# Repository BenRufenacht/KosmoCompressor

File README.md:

# KosmoCompressor
 Kosmo Version of the Moritz Klein Compressor

[Build Docs from Moritz Klein (Erika Synths)](https://www.ericasynths.lv/media/COMPRESSOR_MANUAL.pdf)

Status:   
January 2024 - First run of manufacturing found some minor mistakes that were fixed, but the updates to the pcbs have not been tested.

License:  
[CC-BY-SA](https://creativecommons.org/licenses/by-sa/3.0/)

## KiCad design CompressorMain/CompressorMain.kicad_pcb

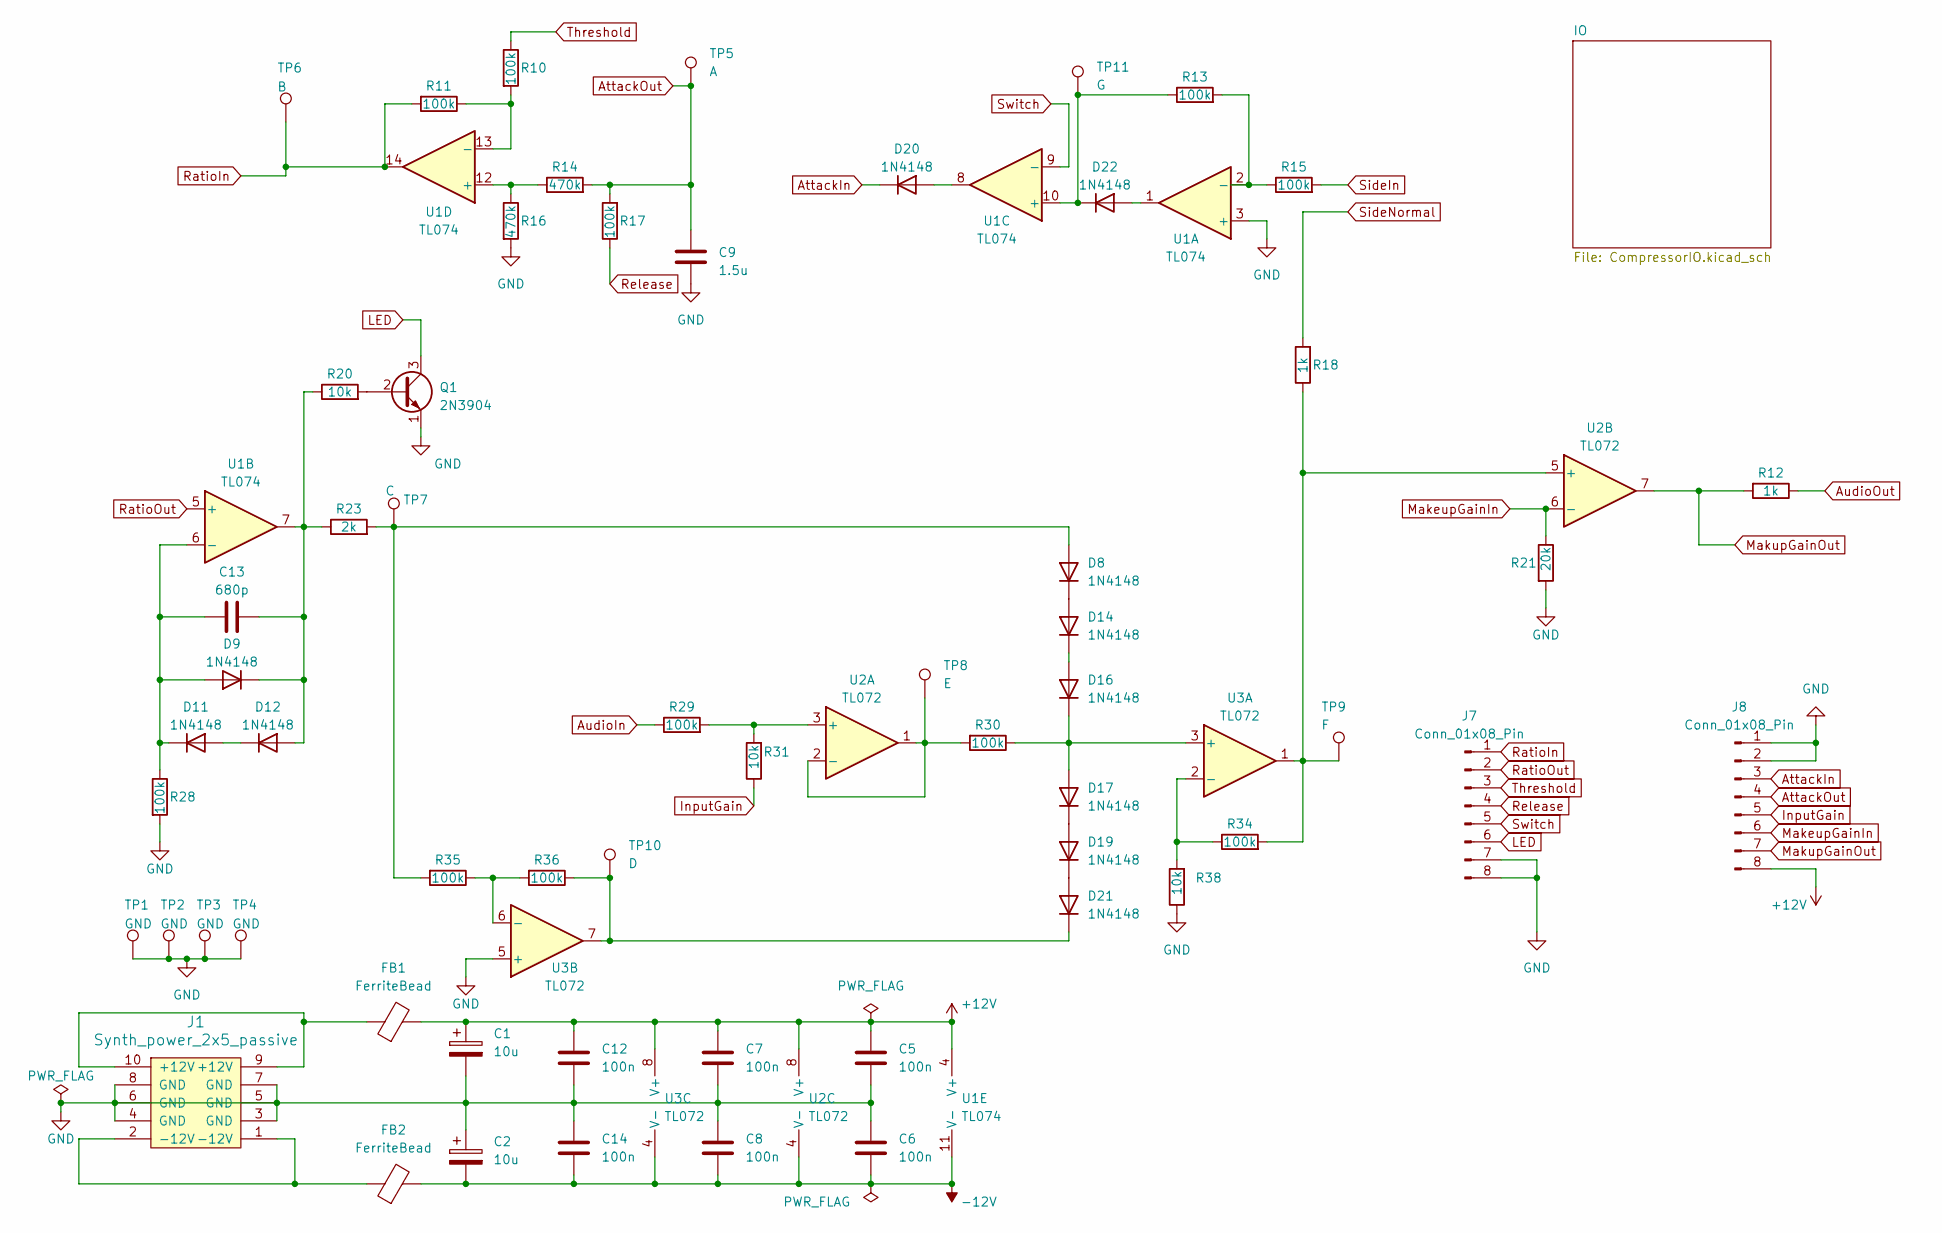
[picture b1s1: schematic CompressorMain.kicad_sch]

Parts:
C1, C2: 10u; CP_Radial_D6.3mm_P2.50mm
C5, C6, C7, C8, C12, C14: 100n; C_Disc_D3.0mm_W1.6mm_P2.50mm
C9: 1.5u; C_Rect_L7.2mm_W4.5mm_P5.00mm_FKS2_FKP2_MKS2_MKP2
C13: 680p; C_Disc_D3.0mm_W1.6mm_P2.50mm
D8, D9, D11, D12, D14, D16, D17, D19, D20, D21, D22: 1N4148; D_DO-35_SOD27_P7.62mm_Horizontal
FB1, FB2: FerriteBead; FB_Axial_L5.0mm_D3.6mm_P10.00mm
J1: Synth_power_2x5_passive; Power_Header
J7, J8: Conn_01x08_Pin; PinSocket_1x08_P2.54mm_Vertical
Q1: 2N3904; TO-92_Inline_Wide
R10, R11, R13, R15, R17, R28, R29, R30, R34, R35, R36: 100k; R_Axial_DIN0207_L6.3mm_D2.5mm_P10.16mm_Horizontal
R12, R18: 1k; R_Axial_DIN0207_L6.3mm_D2.5mm_P10.16mm_Horizontal
R14, R16: 470k; R_Axial_DIN0207_L6.3mm_D2.5mm_P10.16mm_Horizontal
R20, R31, R38: 10k; R_Axial_DIN0207_L6.3mm_D2.5mm_P10.16mm_Horizontal
R21: 20k; R_Axial_DIN0207_L6.3mm_D2.5mm_P10.16mm_Horizontal
R23: 2k; R_Axial_DIN0207_L6.3mm_D2.5mm_P10.16mm_Horizontal
TP1, TP2, TP3, TP4: GND; TestPoint_THTPad_D1.5mm_Drill0.7mm
TP5: A; TestPoint_THTPad_D1.5mm_Drill0.7mm
TP6: B; TestPoint_THTPad_D1.5mm_Drill0.7mm
TP7: C; TestPoint_THTPad_D1.5mm_Drill0.7mm
TP8: E; TestPoint_THTPad_D1.5mm_Drill0.7mm
TP9: F; TestPoint_THTPad_D1.5mm_Drill0.7mm
TP10: D; TestPoint_THTPad_D1.5mm_Drill0.7mm
TP11: G; TestPoint_THTPad_D1.5mm_Drill0.7mm
U1: TL074; DIP-14_W7.62mm_Socket_LongPads
U2, U3: TL072; DIP-8_W7.62mm_Socket_LongPads

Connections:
+12V: C1.1, C5.1, C7.1, C12.1, FB1.2, J8.8, U1.4 (V+), U2.8 (V+), U3.8 (V+)
-12V: C2.2, C6.2, C8.2, C14.2, FB2.2, U1.11 (V-), U2.4 (V-), U3.4 (V-)
AttackIn: D20.1 (K), J8.3
AttackOut: C9.1, J8.4, R14.2, R17.2, TP5.1
AudioIn: R29.1; also elsewhere on the board
AudioOut: R12.1; also elsewhere on the board
GND: C1.2, C2.1, C5.2, C6.1, C7.2, C8.1, C9.2, C12.2, C14.1, J1.3 (GND), J1.4 (GND), J1.5 (GND), J1.6 (GND), J1.7 (GND), J1.8 (GND), J7.7, J7.8, J8.1, J8.2, Q1.1 (E), R16.2, R21.2, R28.2, R38.1, TP1.1, TP2.1, TP3.1, TP4.1, U1.3 (+), U3.5 (+); also elsewhere on the board
InputGain: J8.5, R31.1
LED: J7.6, Q1.3 (C)
MakeupGainIn: J8.6, R21.1, U2.6 (-)
MakupGainOut: J8.7, R12.2, U2.7
unnamed: D8.2 (A), R23.2, R35.2, TP7.1
unnamed: D11.2 (A), D12.1 (K)
unnamed: C13.1, D9.2 (A), D11.1 (K), R28.1, U1.6 (-)
unnamed: C13.2, D9.1 (K), D12.2 (A), R20.1, R23.1, U1.7
unnamed: D8.1 (K), D14.2 (A)
unnamed: D14.1 (K), D16.2 (A)
unnamed: D16.1 (K), D17.2 (A), R30.1, U3.3 (+)
unnamed: D17.1 (K), D19.2 (A)
unnamed: D19.1 (K), D21.2 (A)
unnamed: D20.2 (A), U1.8
unnamed: D21.1 (K), R36.1, TP10.1, U3.7
unnamed: D22.2 (A), U1.1
unnamed: D22.1 (K), R13.1, TP11.1, U1.10 (+)
unnamed: FB1.1, J1.9 (+12V), J1.10 (+12V)
unnamed: FB2.1, J1.1 (-12V), J1.2 (-12V)
unnamed: Q1.2 (B), R20.2
unnamed: R13.2, R15.1, U1.2 (-)
unnamed: R14.1, R16.1, U1.12 (+)
unnamed: R10.2, R11.1, U1.13 (-)
unnamed: R29.2, R31.2, U2.3 (+)
unnamed: R30.2, TP8.1, U2.1, U2.2 (-)
unnamed: R18.1, R34.2, TP9.1, U2.5 (+), U3.1
unnamed: R34.1, R38.2, U3.2 (-)
unnamed: R35.1, R36.2, U3.6 (-)
RatioIn: J7.1, R11.2, TP6.1, U1.14
RatioOut: J7.2, U1.5 (+)
Release: J7.4, R17.1
SideIn: R15.2; also elsewhere on the board
SideNormal: R18.2; also elsewhere on the board
Switch: J7.5, U1.9 (-)
Threshold: J7.3, R10.1

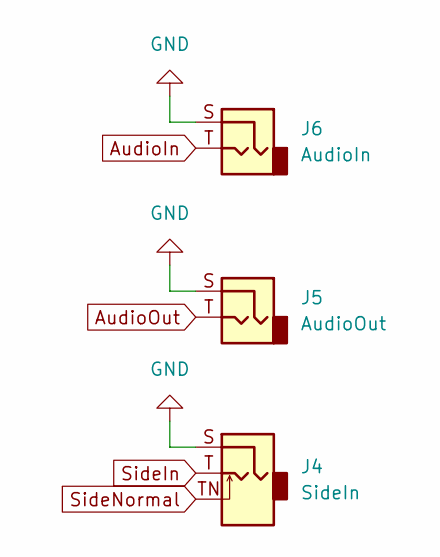
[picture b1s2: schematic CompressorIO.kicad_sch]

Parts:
J4: SideIn; Jack_6.35mm_PJ_629HAN_slots
J5: AudioOut; Jack_6.35mm_PJ_629HAN_slots
J6: AudioIn; Jack_6.35mm_PJ_629HAN_slots

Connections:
AudioIn: J6.T; also elsewhere on the board
AudioOut: J5.T; also elsewhere on the board
GND: J4.S, J5.S, J6.S; also elsewhere on the board
SideIn: J4.T; also elsewhere on the board
SideNormal: J4.TN; also elsewhere on the board

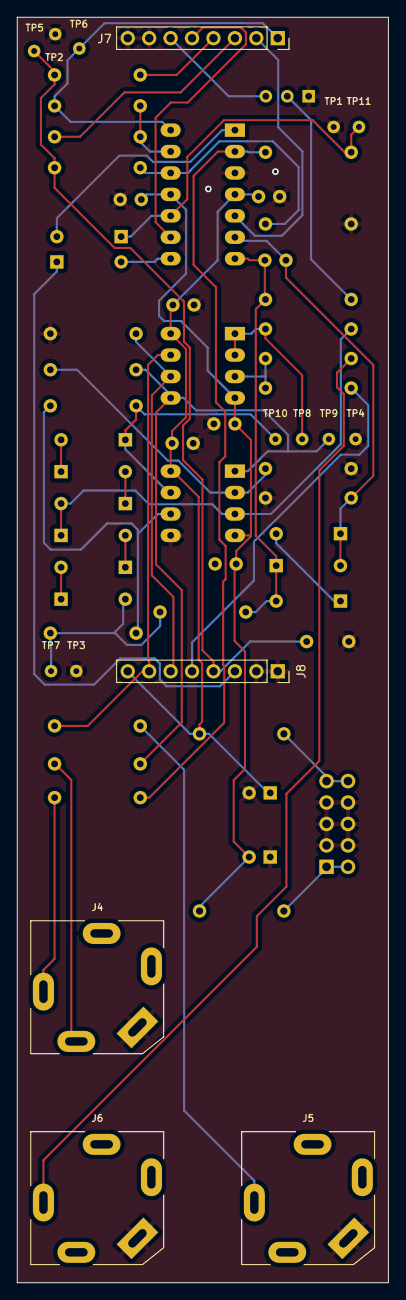
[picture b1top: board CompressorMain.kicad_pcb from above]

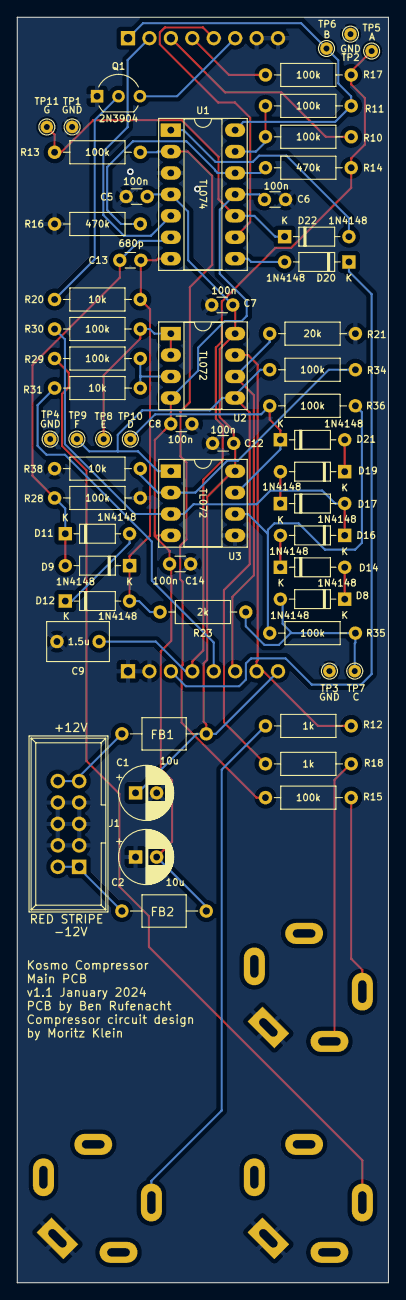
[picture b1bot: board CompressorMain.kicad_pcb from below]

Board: 2 copper layers, 44.0 x 150.0 mm, 64 parts (59 on the bottom side), 42 nets.

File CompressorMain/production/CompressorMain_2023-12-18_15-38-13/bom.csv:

Designator,Footprint,Quantity,Value,LCSC Part #
"C1, C2",CP_Radial_D6.3mm_P2.50mm,2,10u,
"C12, C14, C5, C6, C7, C8",C_Disc_D3.0mm_W1.6mm_P2.50mm,6,100n,
C13,C_Disc_D3.0mm_W1.6mm_P2.50mm,1,680p,
C9,C_Rect_L7.2mm_W2.5mm_P5.00mm_FKS2_FKP2_MKS2_MKP2,1,1.5u,
"D11, D12, D14, D16, D17, D19, D20, D21, D22, D8, D9",D_DO-35_SOD27_P7.62mm_Horizontal,11,1N4148,
"FB1, FB2",FB_Axial_L5.0mm_D3.6mm_P10.00mm,2,FerriteBead,
J1,Power_Header,1,Synth_power_2x5_passive,
J4,Jack_6.35mm_PJ_629HAN_slots,1,SideIn,
J5,Jack_6.35mm_PJ_629HAN_slots,1,AudioOut,
J6,Jack_6.35mm_PJ_629HAN_slots,1,AudioIn,
"J7, J8",PinSocket_1x08_P2.54mm_Vertical,2,Conn_01x08_Pin,
Q1,TO-92_Inline_Wide,1,2N3904,
"R10, R11, R13, R15, R17, R28, R29, R30, R34, R35, R36",R_Axial_DIN0207_L6.3mm_D2.5mm_P10.16mm_Horizontal,11,100k,
"R12, R18",R_Axial_DIN0207_L6.3mm_D2.5mm_P10.16mm_Horizontal,2,1k,
"R14, R16",R_Axial_DIN0207_L6.3mm_D2.5mm_P10.16mm_Horizontal,2,470k,
"R20, R31, R38",R_Axial_DIN0207_L6.3mm_D2.5mm_P10.16mm_Horizontal,3,10k,
R21,R_Axial_DIN0207_L6.3mm_D2.5mm_P10.16mm_Horizontal,1,20k,
R23,R_Axial_DIN0207_L6.3mm_D2.5mm_P10.16mm_Horizontal,1,2k,
U1,DIP-14_W7.62mm_Socket_LongPads,1,TL074,
"U2, U3",DIP-8_W7.62mm_Socket_LongPads,2,TL072,

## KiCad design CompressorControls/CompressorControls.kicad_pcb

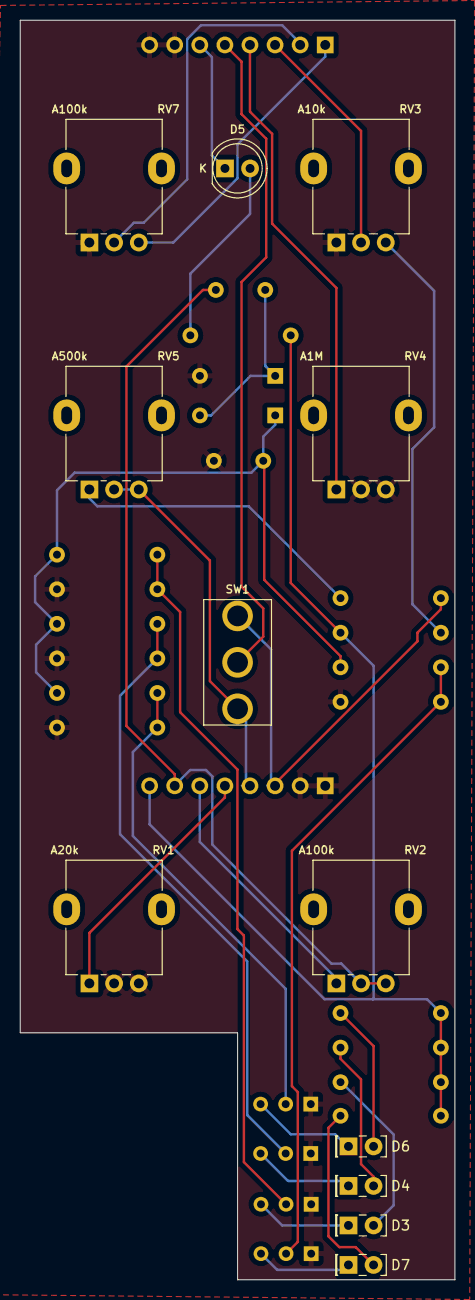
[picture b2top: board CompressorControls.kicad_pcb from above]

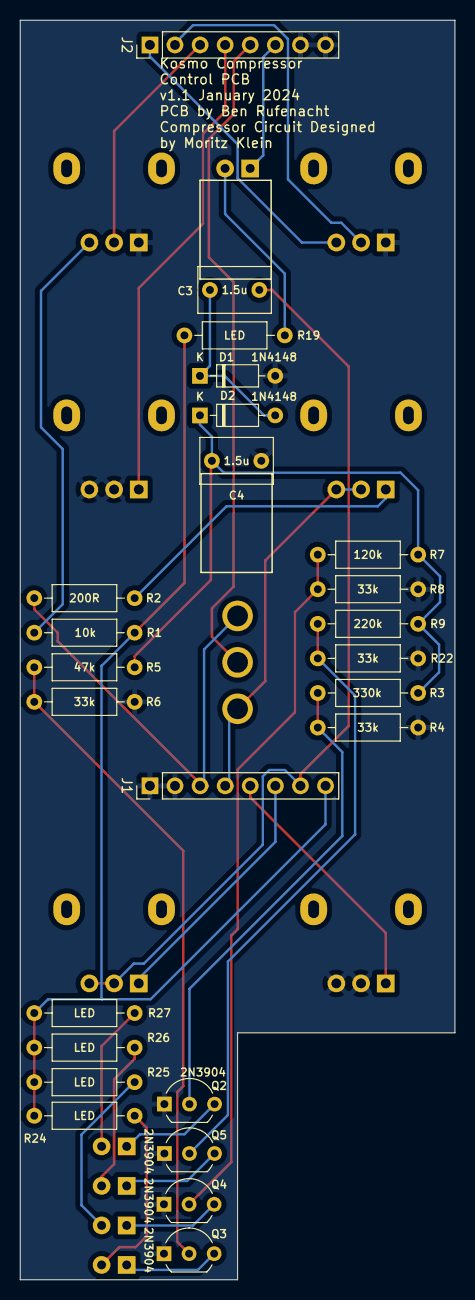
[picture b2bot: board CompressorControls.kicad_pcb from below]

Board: 2 copper layers, 44.0 x 127.5 mm, 37 parts (25 on the bottom side), 30 nets.

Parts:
C3, C4: 1.5u; C_Rect_L7.2mm_W4.5mm_P5.00mm_FKS2_FKP2_MKS2_MKP2
D1, D2: 1N4148; D_DO-35_SOD27_P7.62mm_Horizontal
D3, D7: LED_green; LED_Rectangular_W5.0mm_H2.0mm
D4, D6: LED; LED_Rectangular_W5.0mm_H2.0mm
D5: LED_green; LED_D5.0mm
J1, J2: Conn_01x08_Pin; PinHeader_1x08_P2.54mm_Vertical
Q2, Q3, Q4, Q5: 2N3904; TO-92_Inline_Wide
R1: 10k; R_Axial_DIN0207_L6.3mm_D2.5mm_P10.16mm_Horizontal
R2: 200R; R_Axial_DIN0207_L6.3mm_D2.5mm_P10.16mm_Horizontal
R3: 330k; R_Axial_DIN0207_L6.3mm_D2.5mm_P10.16mm_Horizontal
R4, R6, R8, R22: 33k; R_Axial_DIN0207_L6.3mm_D2.5mm_P10.16mm_Horizontal
R5: 47k; R_Axial_DIN0207_L6.3mm_D2.5mm_P10.16mm_Horizontal
R7: 120k; R_Axial_DIN0207_L6.3mm_D2.5mm_P10.16mm_Horizontal
R9: 220k; R_Axial_DIN0207_L6.3mm_D2.5mm_P10.16mm_Horizontal
R19, R24, R25, R26, R27: LED; R_Axial_DIN0207_L6.3mm_D2.5mm_P10.16mm_Horizontal
RV1: A20k; Potentiometer_Alpha_RD901F-40-00D_Single_Vertical_centered
RV2, RV7: A100k; Potentiometer_Alpha_RD901F-40-00D_Single_Vertical_centered
RV3: A10k; Potentiometer_Alpha_RD901F-40-00D_Single_Vertical_centered
RV4: A1M; Potentiometer_Alpha_RD901F-40-00D_Single_Vertical_centered
RV5: A500k; Potentiometer_Alpha_RD901F-40-00D_Single_Vertical_centered
SW1: SW_SPDT; SPDT-toggle-switch-1M-series

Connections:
+12V: J1.8, R1.1, R19.1, R24.1, R25.1, R26.1, R27.1
AttackIn: J1.3, R2.2, SW1.3 (C)
AttackOut: J1.4, RV5.2, RV5.3, SW1.1 (A)
GND: C4.1, D1.2 (A), J1.1, J1.2, J2.7, J2.8, Q2.1 (E), Q3.1 (E), Q4.1 (E), Q5.1 (E), R4.2, R6.2, R8.2, R22.2, RV1.2, RV1.3, RV3.1, RV4.2, RV4.3, RV7.1
InputGain: J1.5, RV1.1
LED: D5.1 (K), J2.6
MakeupGainIn: J1.6, RV2.1
MakupGainOut: C3.1, J1.7, RV2.2, RV2.3
unnamed: C3.2, D1.1 (K), D2.2 (A)
unnamed: C4.2, D2.1 (K), R3.2, R5.2, R7.2, R9.2
unnamed: D3.2 (A), R25.2
unnamed: D3.1 (K), Q4.3 (C)
unnamed: D4.2 (A), R26.2
unnamed: D4.1 (K), Q5.3 (C)
unnamed: D5.2 (A), R19.2
unnamed: D6.2 (A), R27.2
unnamed: D6.1 (K), Q2.3 (C)
unnamed: D7.2 (A), R24.2
unnamed: D7.1 (K), Q3.3 (C)
unnamed: Q2.2 (B), R3.1, R4.1
unnamed: Q3.2 (B), R5.1, R6.1
unnamed: Q4.2 (B), R7.1, R8.1
unnamed: Q5.2 (B), R9.1, R22.1
unnamed: R1.2, RV3.3
unnamed: R2.1, RV5.1
RatioIn: J2.1, RV7.3
RatioOut: J2.2, RV7.2
Release: J2.4, RV4.1
Switch: J2.5, SW1.2 (B)
Threshold: J2.3, RV3.2

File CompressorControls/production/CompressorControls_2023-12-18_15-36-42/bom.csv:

Designator,Footprint,Quantity,Value,LCSC Part #
"C3, C4",C_Rect_L7.2mm_W2.5mm_P5.00mm_FKS2_FKP2_MKS2_MKP2,2,1.5u,
"D1, D2",D_DO-35_SOD27_P7.62mm_Horizontal,2,1N4148,
"D3, D7",LED_Rectangular_W5.0mm_H2.0mm,2,LED_green,
"D4, D6",LED_Rectangular_W5.0mm_H2.0mm,2,LED,
D5,LED_D5.0mm,1,LED_green,
"J1, J2",PinHeader_1x08_P2.54mm_Vertical,2,Conn_01x08_Pin,
"Q2, Q3, Q4, Q5",TO-92_Inline_Wide,4,2N3904,
R1,R_Axial_DIN0207_L6.3mm_D2.5mm_P10.16mm_Horizontal,1,10k,
"R19, R24, R25, R26, R27",R_Axial_DIN0207_L6.3mm_D2.5mm_P10.16mm_Horizontal,5,LED,
R2,R_Axial_DIN0207_L6.3mm_D2.5mm_P10.16mm_Horizontal,1,200R,
"R22, R4, R6, R8",R_Axial_DIN0207_L6.3mm_D2.5mm_P10.16mm_Horizontal,4,33k,
R3,R_Axial_DIN0207_L6.3mm_D2.5mm_P10.16mm_Horizontal,1,330k,
R5,R_Axial_DIN0207_L6.3mm_D2.5mm_P10.16mm_Horizontal,1,47k,
R7,R_Axial_DIN0207_L6.3mm_D2.5mm_P10.16mm_Horizontal,1,120k,
R9,R_Axial_DIN0207_L6.3mm_D2.5mm_P10.16mm_Horizontal,1,220k,
RV1,Potentiometer_Alpha_RD901F-40-00D_Single_Vertical_centered,1,A20k,
"RV2, RV4",Potentiometer_Alpha_RD901F-40-00D_Single_Vertical_centered,2,A100k,
RV3,Potentiometer_Alpha_RD901F-40-00D_Single_Vertical_centered,1,A10k,
RV5,Potentiometer_Alpha_RD901F-40-00D_Single_Vertical_centered,1,A500k,
RV6,Potentiometer_Alpha_RD901F-40-00D_Single_Vertical_centered,1,A1M,
SW1,SPDT-toggle-switch-1M-series,1,SW_SPDT,
